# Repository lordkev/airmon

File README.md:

# AirMon

A USB-powered home air-quality monitor built around the **Keyestudio 2.8-inch ESP32-WROOM-32E touchscreen board**, with a small sensor carrier, printable enclosure, offline web dashboard, HTTP API, and optional Home Assistant integration.

**Prototype r0.1 — digital design, not yet physically validated.** The exact display-board mating connector and PMSA003I socket fit must be confirmed before ordering the PCB. Firmware compilation and CAD checks do not establish hardware operation. See the [validation ledger](docs/VALIDATION.md) for completed checks and remaining release gates.

*CAD rendering of the full enclosure. LCD values are illustrative; this is not a photograph or firmware screenshot. Body: 100 × 82 × 44 mm, excluding the stand; shallow body: 100 × 82 × 30 mm.*

| Measurement | Sensor | Configuration |
|---|---|---|
| Temperature / relative humidity | SHT40 | Included on the carrier |
| PM1 / PM2.5 / PM10 | PMSA003I, Adafruit 4505 | Optional removable module |
| Actual CO₂ | SCD40, Adafruit 5187 | Optional STEMMA QT module |
| VOC / NOx indices | SGP41, Adafruit 6455 | Optional STEMMA QT module |

All sensors costing more than about $10 are optional. Add the PM module to meet the original temperature/humidity/PM2.5 minimum; the lowest-cost build measures temperature and humidity only. Gas indices do not identify individual chemicals, and AirMon does not replace a smoke or carbon-monoxide alarm.

## The circuit board

*Native KiCad rendering of the routed 42 × 55 mm carrier, showing the regulator, protection, connectors, and test points. The SHT40 is on the opposite face of the extended tongue.*

*Mechanical rendering with the optional PMSA003I installed. Vendor modules and this view's carrier use simplified clearance envelopes; use the KiCad source and STEP for component-level details.*

## Build and use

1. Read [hardware and ordering](docs/HARDWARE.md), including the two connector checks.
2. Use the [BOM workbook](hardware/BOM.xlsx), [assembly CSV](hardware/assembly-bom.csv), and [purchasing CSV](hardware/purchasing-bom.csv).
3. Follow [printing and assembly](docs/ASSEMBLY.md), with the exploded CAD view.
4. [Build or flash the firmware](docs/FIRMWARE.md), then [configure and use AirMon](docs/USE.md).
5. Integrate through the [HTTP API](docs/API.md) or [MQTT/Home Assistant](docs/HOME_ASSISTANT.md).

## Deliverables

| Deliverable | Files |
|---|---|
| Editable electronics | [KiCad PCB](hardware/airmon.kicad_pcb), [schematic](hardware/airmon.kicad_sch), local libraries in `hardware/` |
| Manufacturing | [Gerber/drill ZIP](hardware/exports/airmon-gerbers.zip), [schematic PDF](hardware/exports/schematic.pdf), [assembly drawings and placement](hardware/exports/) |
| Mechanical | [PCB STEP](hardware/exports/airmon.step), [OpenSCAD source](enclosure/airmon.scad), [seven STL exports](enclosure/stl/) |
| Firmware | [ESP-IDF source](firmware/), [prototype binaries](release/firmware/) |
| Checks | [Validation ledger](docs/VALIDATION.md), [ERC](hardware/exports/erc.txt), [DRC](hardware/exports/drc.txt), [mesh checks](enclosure/mesh-validation.json), [CAD clearances](enclosure/clearance-validation.json) |
| Reproduction | [Development guide](docs/DEVELOPMENT.md), [requirements](PROMPT.md), [third-party notices](THIRD_PARTY.md) |

The project uses local Wi-Fi and HTTP. No cloud account or internet connection is required for normal readings; internet access is only used for optional clock synchronization and configured external services. History consists of 24 hours of one-minute means in RAM and resets at reboot.

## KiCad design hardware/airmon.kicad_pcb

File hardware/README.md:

# AirMon carrier — prototype r0.1

Open `airmon.kicad_sch` and `airmon.kicad_pcb` in KiCad 10. Local symbols, footprints, and STEP models are included. The carrier is 42 × 55 mm overall, with a ventilated SHT40 tongue and optional PMSA003I mating socket.

Read [hardware and ordering](../docs/HARDWARE.md) before sending files to a manufacturer. **Exact display-board connector identification and the supplied PM socket fit remain unresolved physical checks.** ERC/DRC results apply to the digital design and do not remove these release gates.

- `exports/airmon-gerbers.zip`: copper, mask, silk, paste, outline, PTH and NPTH drill files.
- `exports/schematic.pdf`, `assembly-top.pdf`, `assembly-bottom.pdf`: electrical and assembly drawings.
- `exports/footprint-fit-1to1.pdf`: print at actual size to compare the supplied PM socket.
- `exports/placement-smt.csv`: SMT placement; J1/J2 require through-hole assembly separately.
- `BOM.xlsx`, `assembly-bom.csv`, `purchasing-bom.csv`: components and full purchasing data.
- `exports/airmon.step`: assembled carrier geometry.

J5 pad numbering follows Plantower, not the generic numbering in the Adafruit reference design. It must be checked against the supplied mating socket. Physical module models in enclosure illustrations are simplified envelopes.

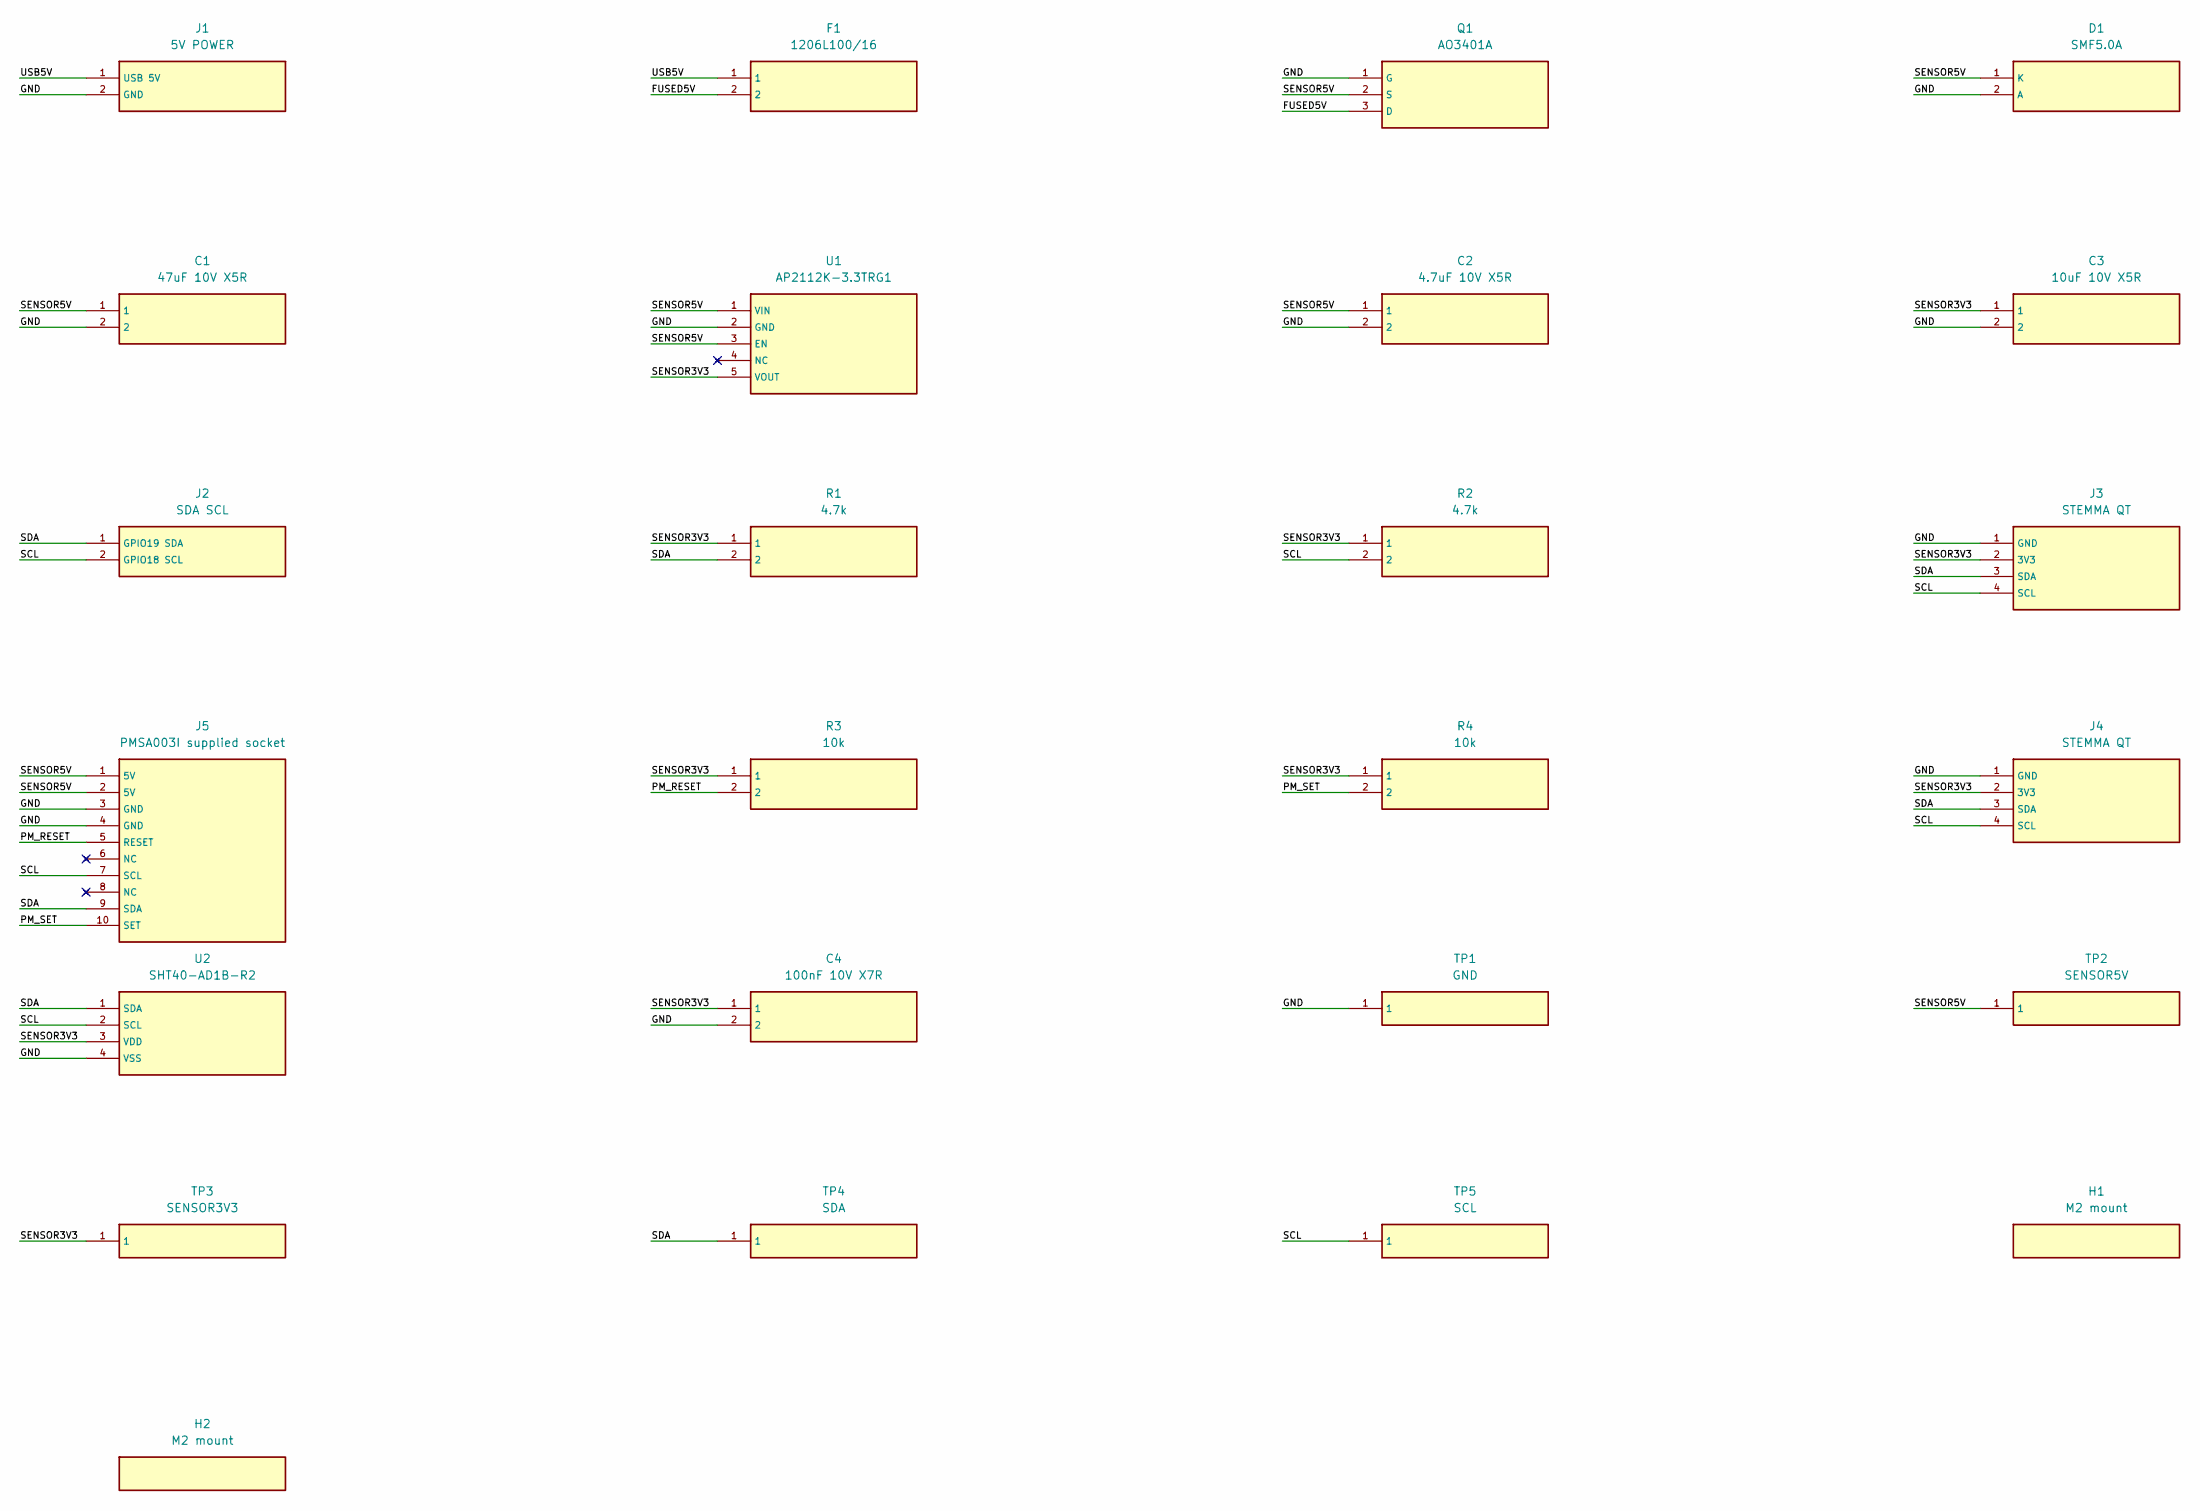
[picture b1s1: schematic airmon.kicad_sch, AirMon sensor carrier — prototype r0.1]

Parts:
C1: 47uF 10V X5R; C_1210_3225Metric
C2: 4.7uF 10V X5R; C_0603_1608Metric
C3: 10uF 10V X5R; C_0603_1608Metric
C4: 100nF 10V X7R; C_0603_1608Metric
D1: SMF5.0A; D_SOD-123F
F1: 1206L100/16; Fuse_1206_3216Metric
H1, H2: M2 mount; MountingHole_2.2mm_M2
J1: 5V POWER; JST_PH_B2B-PH-K_1x02_P2.00mm_Vertical
J2: SDA SCL; JST_PH_B2B-PH-K_1x02_P2.00mm_Vertical
J3, J4: STEMMA QT; JST_SH_SM04B-SRSS-TB_1x04-1MP_P1.00mm_Horizontal
J5: PMSA003I supplied socket; PMSA003I_SuppliedSocket
Q1: AO3401A; SOT-23
R1, R2: 4.7k; R_0603_1608Metric
R3, R4: 10k; R_0603_1608Metric
TP1: GND; TestPoint_Pad_D1.0mm
TP2: SENSOR5V; TestPoint_Pad_D1.0mm
TP3: SENSOR3V3; TestPoint_Pad_D1.0mm
TP4: SDA; TestPoint_Pad_D1.0mm
TP5: SCL; TestPoint_Pad_D1.0mm
U1: AP2112K-3.3TRG1; SOT-23-5
U2: SHT40-AD1B-R2; Sensirion_DFN-4_1.5x1.5mm_P0.8mm_SHT4x_NoCentralPad

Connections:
FUSED5V: F1.2, Q1.3 (D)
GND: C1.2, C2.2, C3.2, C4.2, D1.2 (A), J1.2 (GND), J3.1 (GND), J4.1 (GND), J5.3 (GND), J5.4 (GND), Q1.1 (G), TP1.1, U1.2 (GND), U2.4 (VSS)
PM_RESET: J5.5 (RESET), R3.2
PM_SET: J5.10 (SET), R4.2
SCL: J2.2 (GPIO18 SCL), J3.4 (SCL), J4.4 (SCL), J5.7 (SCL), R2.2, TP5.1, U2.2 (SCL)
SDA: J2.1 (GPIO19 SDA), J3.3 (SDA), J4.3 (SDA), J5.9 (SDA), R1.2, TP4.1, U2.1 (SDA)
SENSOR3V3: C3.1, C4.1, J3.2 (3V3), J4.2 (3V3), R1.1, R2.1, R3.1, R4.1, TP3.1, U1.5 (VOUT), U2.3 (VDD)
SENSOR5V: C1.1, C2.1, D1.1 (K), J5.1 (5V), J5.2 (5V), Q1.2 (S), TP2.1, U1.1 (VIN), U1.3 (EN)
USB5V: F1.1, J1.1 (USB 5V)

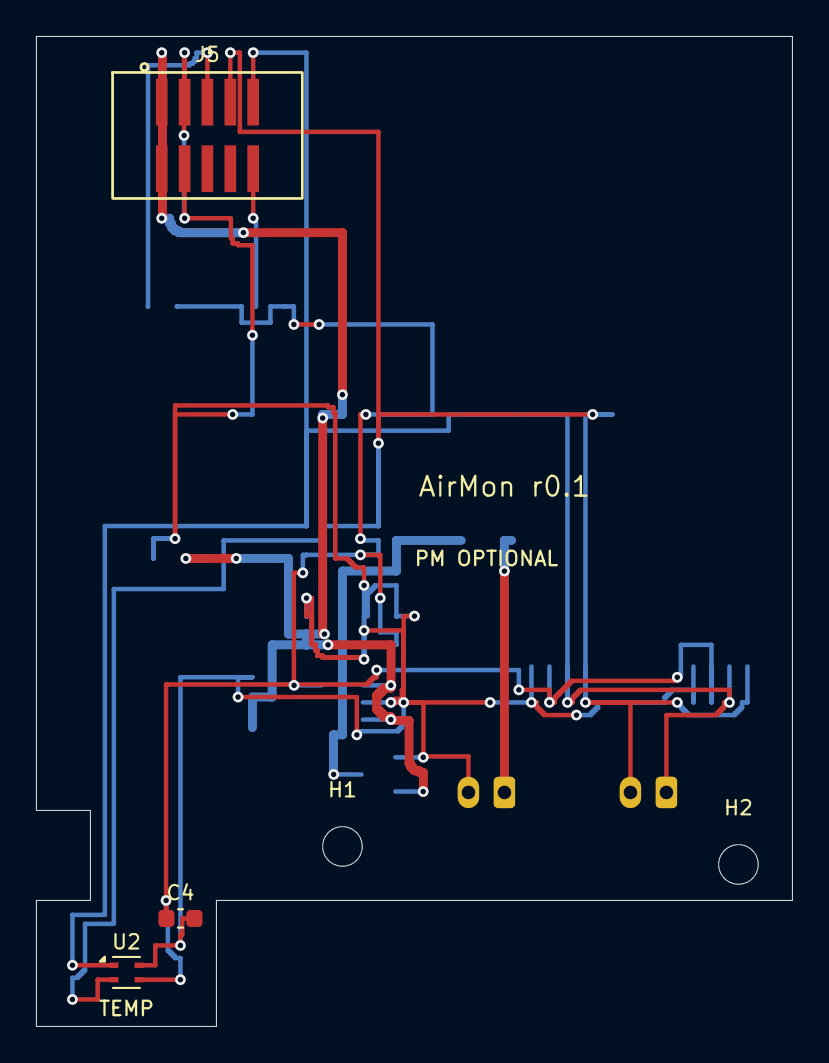
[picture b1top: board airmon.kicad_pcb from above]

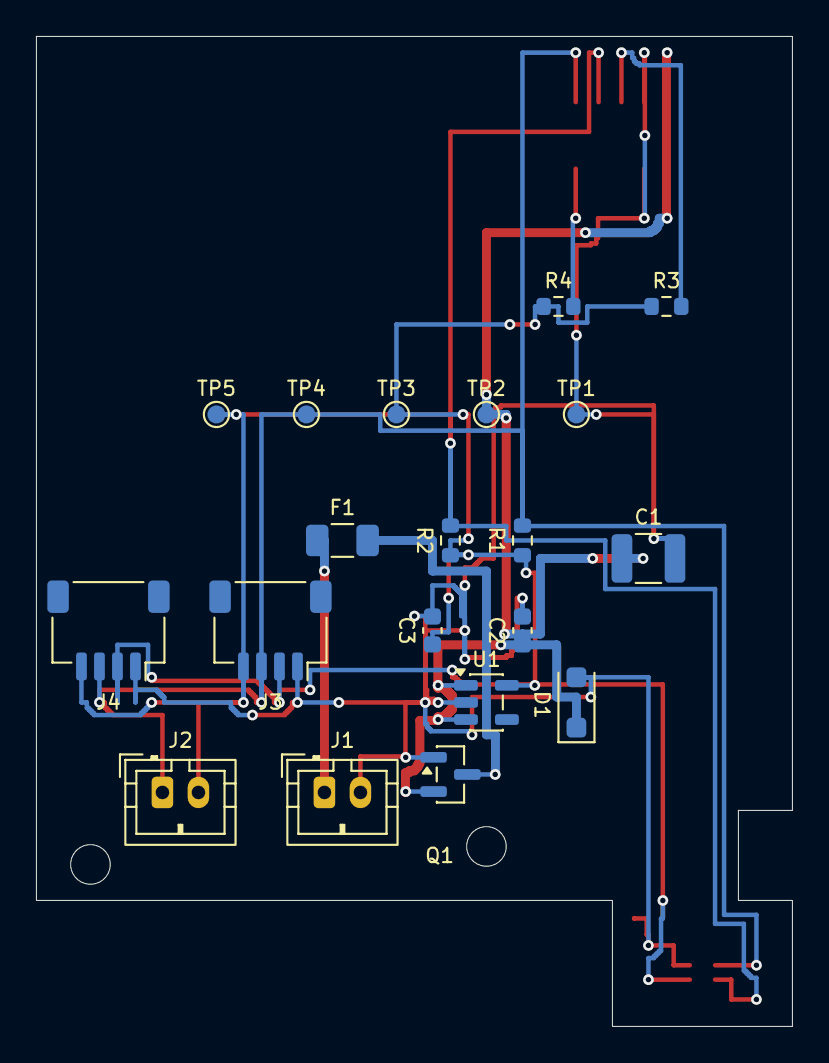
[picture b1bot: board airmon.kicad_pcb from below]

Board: 2 copper layers, 42.0 x 55.0 mm, 25 parts (20 on the bottom side), 9 nets.

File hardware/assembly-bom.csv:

"References","Qty","Part","Manufacturer","MPN","Package","Unit USD","Line USD","Price basis","Installation","Assembly notes","Source URL","Date"
"U1","1","3.3 V 600 mA LDO","Diodes Incorporated","AP2112K-3.3TRG1","SOT-23-5","0.45","0.45","Estimate","Required","SMT bottom","https://www.diodes.com/assets/Datasheets/AP2112.pdf","2026-09-06"
"U2","1","Temperature and humidity","Sensirion","SHT40-AD1B-R2","DFN-4 1.5 x 1.5 mm","3.5","3.5","Estimate","Required","SMT top; no wash or coating over sensor","https://sensirion.com/products/catalog/SHT40","2026-09-06"
"Q1","1","Reverse input polarity MOSFET","Alpha & Omega","AO3401A","SOT-23","0.25","0.25","Estimate","Required","SMT bottom; source faces protected rail","https://www.aosmd.com/products/mosfets/low-voltage-mosfets-1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","2026-09-06"
"F1","1","1 A resettable fuse","Littelfuse","1206L100/16YR","1206","0.8","0.8","Estimate","Required","SMT bottom","https://www.littelfuse.com/products/polyswitch-resettable-pp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","2026-09-06"
"D1","1","5 V transient suppressor","Littelfuse","SMF5.0A","SOD-123F","0.4","0.4","Estimate","Required","SMT bottom; cathode to SENSOR5V","https://www.digikey.com/en/products/detail/littelfuse-inc/SM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","2026-09-06"
"C1","1","47 uF 10 V X5R bulk capacitor","Murata","GRM32ER61A476KE20L","1210","0.85","0.85","Estimate","Required","SMT bottom","https://www.murata.com/en-us/products/productdetail?partno=G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","2026-09-06"
"C2","1","4.7 uF 10 V X5R input capacitor","Murata","GRM188R61A475KE15D","0603","0.15","0.15","Estimate","Required","SMT bottom","https://www.murata.com/en-us/products/productdetail?partno=G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","2026-09-06"
"C3","1","10 uF 10 V X5R output capacitor","Murata","GRM188R61A106KE69D","0603","0.2","0.2","Estimate","Required","SMT bottom","https://www.murata.com/en-us/products/productdetail?partno=G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","2026-09-06"
"C4","1","100 nF 16 V X7R bypass capacitor","Murata","GRM188R71C104KA01D","0603","0.05","0.05","Estimate","Required","SMT top","https://www.murata.com/en-us/products/productdetail?partno=G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","2026-09-06"
"R1 R2","2","4.7 kohm 1% I2C pull-up","Yageo","RC0603FR-074K7L","0603","0.03","0.06","Estimate","Required","SMT bottom","https://www.yageo.com/en/ProductSearch","2026-09-06"
"R3 R4","2","10 kohm 1% PM control pull-up","Yageo","RC0603FR-0710KL","0603","0.03","0.06","Estimate","Required","SMT bottom","https://www.yageo.com/en/ProductSearch","2026-09-06"
"J1 J2","2","Keyed 2-pin power / I2C connector","JST","B2B-PH-K-S(LF)(SN)","PH 2.00 mm vertical THT","0.5","1","Estimate","Required","Through-hole bottom; quote THT assembly separately","https://www.jst-mfg.com/product/index.php?series=199","2026-09-06"
"J3 J4","2","STEMMA QT / Qwiic socket","JST","SM04B-SRSS-TB(LF)(SN)","SH 1.00 mm horizontal SMT","0.7","1.4","Estimate","Required","SMT bottom; pin 1 GND, 2 3V3, 3 SDA, 4 SCL","https://www.jst-mfg.com/product/index.php?series=231","2026-09-06"
"J5","1","PMSA003I paired mating socket","Supplied with module","Adafruit 4505 supplied socket","2 x 5 1.27 mm SMT","","","Included in optional module kit","Optional PM","Consigned or hand-installed socket; verify land pattern against supplied part","https://www.adafruit.com/product/4505","2026-09-06"
